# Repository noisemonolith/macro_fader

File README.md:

# Eurorack macro fader module
designed by noise monolith\
[noisemonolith.com](https://noisemonolith.com)\
2021

## Functions
The module features a 45mm fader to set a fixed CV and send it to 3 different inputs CV inputs at once. This offers fast and easy macro controls especially during performances. An example would be to map wave shape, filter cutoff and volume of a synth voice to the fader.

### Fader:
Sets the CV out depending on the mode switch.

### Mode switch:
Changes between uni- and bipolar modes. CV range is 0V - 5V in unipolar mode and -5V - 5V in bipolar mode.

### CV LED:
The LED indicates the current CV. Red = 5V, Off = 0V, Green = -5V.

### CV Outputs:
3 buffered identical outputs providing the CV set by the fader.

## Tools
schematics and pcb created with eagle cad

## Schematics

## License
This project is licensed under the [GNU Lesser General Public License Version 3](https://www.gnu.org/licenses/lgpl-3.0.html)

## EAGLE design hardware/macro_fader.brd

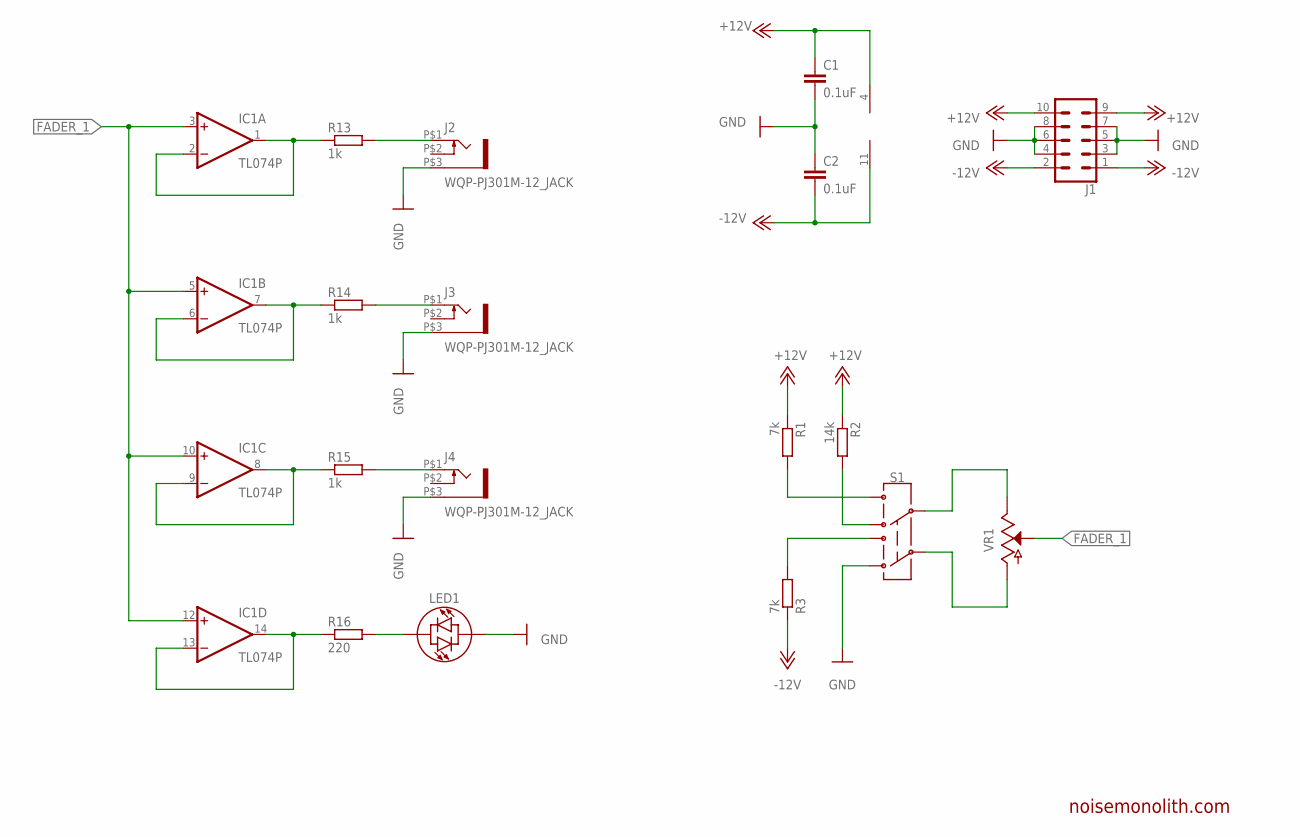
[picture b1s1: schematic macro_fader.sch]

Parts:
C1, C2: 0.1uF; C050-025X075
IC1: TL074P; DIL14
J1: CONN_05X2SHD; 2X5-SHROUDED
J2, J3, J4: WQP-PJ301M-12_JACK
LED1: A-1076_RED-GREEN-LED-3MM3MM; A-1076_RED-GREEN-LED-3MM
R1, R3: 7k; 0207/7
R2: 14k; 0207/7
R13, R14, R15: 1k; 0207/7
R16: 220; 0207/7
S1: A-4568_MINITOGGLESWITCH_DPDT_ON-ON
VR1: F4505-N0SC2B10K

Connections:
+12V: C1.1, IC1.4 (V+), J1.9, J1.10, R1.1, R2.1
-12V: C2.2, IC1.11 (V-), J1.1, J1.2, R3.1
FADER_1: IC1.3 (+IN), IC1.5 (+IN), IC1.10 (+IN), IC1.12 (+IN), VR1.2
GND: C1.2, C2.1, J1.3, J1.4, J1.5, J1.6, J1.7, J1.8, J2.P$3 (1), J3.P$3 (1), J4.P$3 (1), LED1.G (GREEN), S1.6
unnamed: S1.2, VR1.1
unnamed: S1.5, VR1.3
unnamed: R1.2, S1.1
unnamed: IC1.1 (OUT), IC1.2 (-IN), R13.1
unnamed: R2.2, S1.3
unnamed: J2.P$1 (2), R13.2
unnamed: R3.2, S1.4
unnamed: IC1.6 (-IN), IC1.7 (OUT), R14.1
unnamed: J3.P$1 (2), R14.2
unnamed: IC1.8 (OUT), IC1.9 (-IN), R15.1
unnamed: J4.P$1 (2), R15.2
unnamed: IC1.13 (-IN), IC1.14 (OUT), R16.1
unnamed: LED1.R (RED), R16.2

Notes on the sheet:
noisemonolith.com

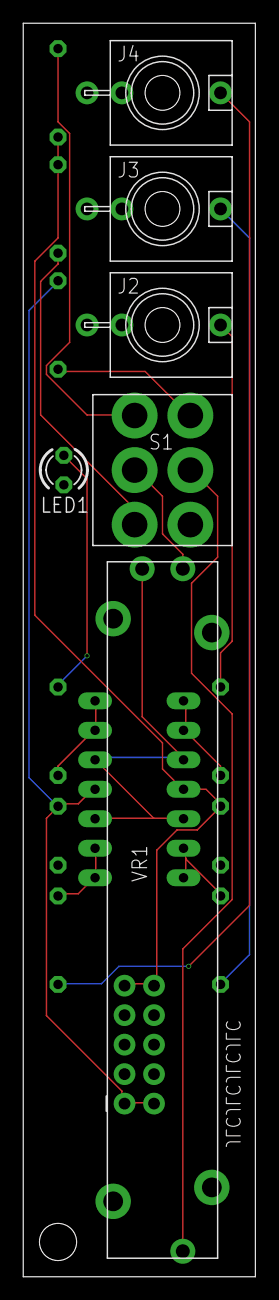
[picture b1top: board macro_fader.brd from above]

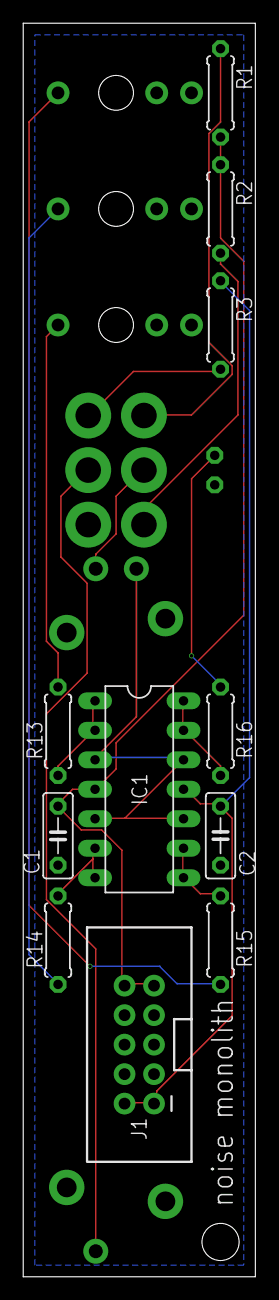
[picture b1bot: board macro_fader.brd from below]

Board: 2 copper layers, 20.0 x 108.0 mm, 17 parts (11 on the bottom side), 17 nets.

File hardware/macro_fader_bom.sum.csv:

Value,Device,Package,Part
0.1uF,C-EU050-025X075,C050-025X075,1
14k,R-EU_0207/7,0207/7,1
220,R-EU_0207/7,0207/7,1
A-1076_RED-GREEN-LED-3MM3MM,A-1076_RED-GREEN-LED-3MM,custom_parts,1
A-4568_MINITOGGLESWITCH_DPDT_ON-ON,A-4568_MINITOGGLESWITCH_DPDT_ON-ON,A-4568_MINITOGGLESWITCH_DPDT_ON-ON,1
CONN_05X2SHD,2X5-SHROUDED,SparkFun-Connectors,1
F4505-N0SC2B10K,F4505-N0SC2B10K,F4505-N0SC2B10K,1
TL074P,TL074P,DIL14,1
7k,R-EU_0207/7,0207/7,2
1k,R-EU_0207/7,0207/7,3
WQP-PJ301M-12_JACK,WQP-PJ301M-12_JACK,WQP-PJ301M-12_JACK,3

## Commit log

2021-10-13 add first production version of the module
2022-09-03 add missing board file for the front panel

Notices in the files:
parts and their libraries:
SparkFun-Connectors: Licensing: Creative Commons ShareAlike 4.0 International - https://creativecommons.org/licenses/by-sa/4.0
